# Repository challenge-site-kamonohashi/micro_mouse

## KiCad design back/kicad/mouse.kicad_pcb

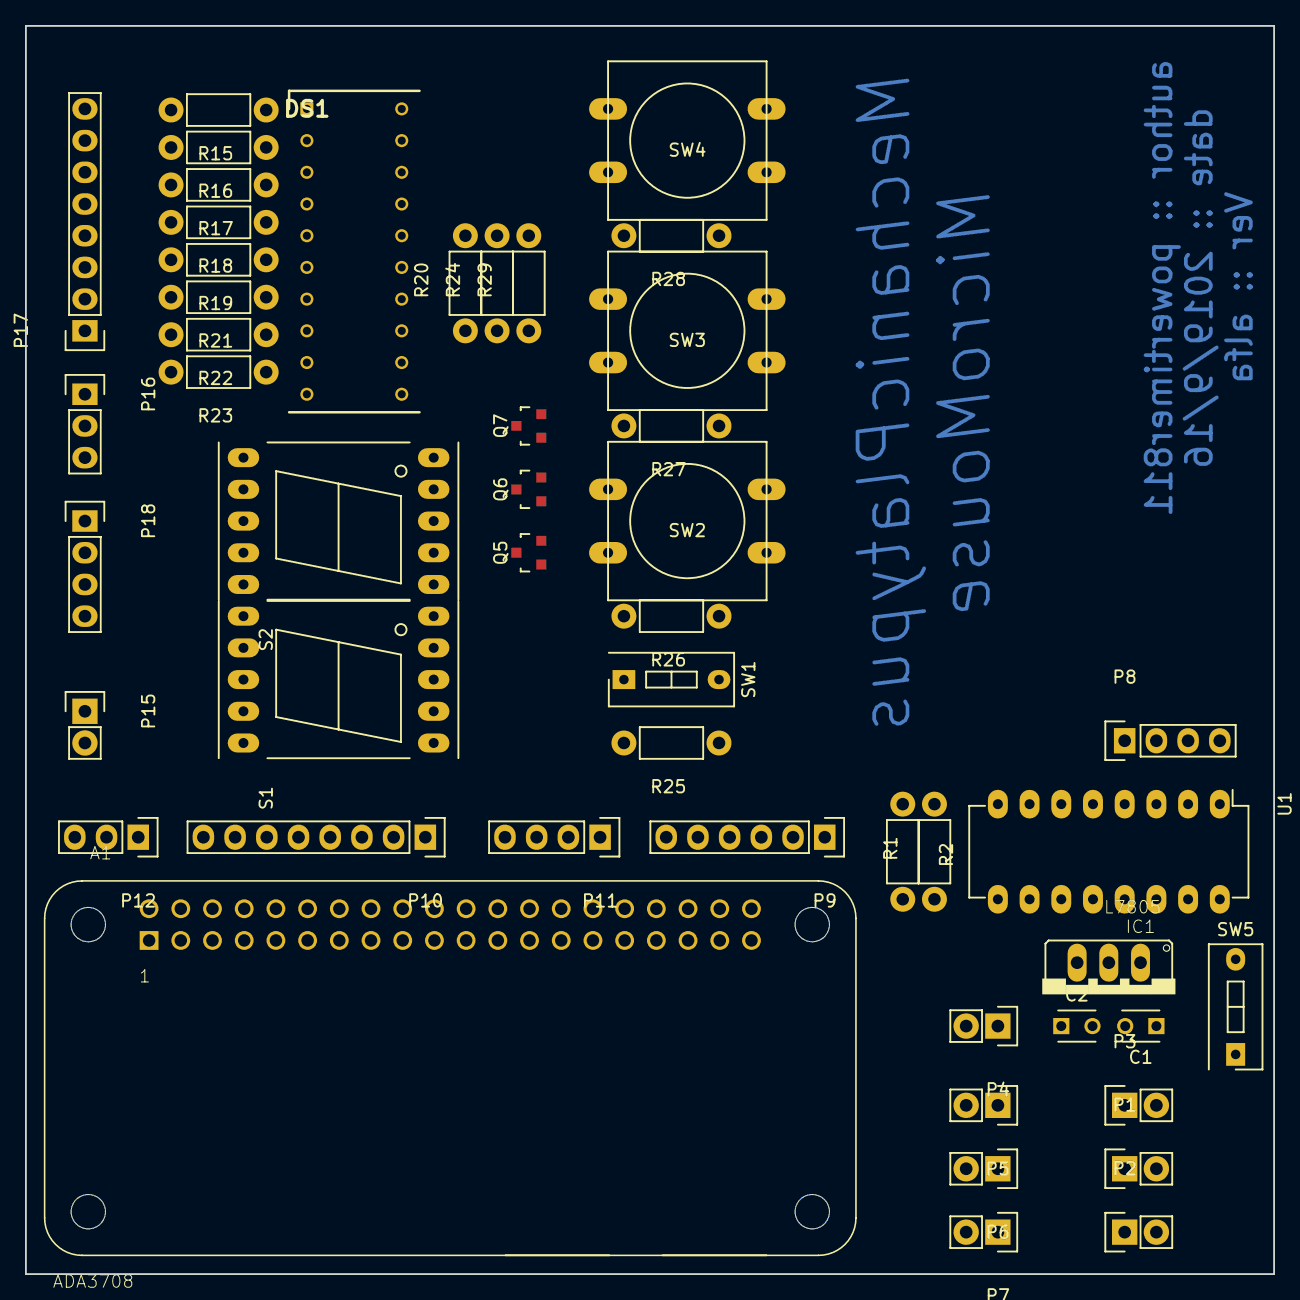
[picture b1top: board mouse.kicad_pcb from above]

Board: 2 copper layers, 100.0 x 100.0 mm, 49 parts (0 on the bottom side), 62 nets, no tracks yet.

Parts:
A1: ADA3708; ADA3708_RPI-ZERO
C1: 0.33uF; C_Disc_D3_P2.5
C2: 0.1uF; C_Disc_D3_P2.5
DS1: OSX10201-GYR1; DIPS760W45P254L2550H815Q20N
IC1: L7805; 78XXS
P1, P2: SOURCE_12v; Socket_Strip_Straight_1x02
P3: battery 12v; Socket_Strip_Straight_1x02
P4, P5, P6, P7: SOURCE_5v; Socket_Strip_Straight_1x02
P8: IR_CONN; Socket_Strip_Straight_1x04
P9: MOTOR_CONTROL; Socket_Strip_Straight_1x06
P10, P17: LED_CONN; Socket_Strip_Straight_1x08
P11, P18: SW_CONN; Socket_Strip_Straight_1x04
P12, P16: LED_K_CONN; Socket_Strip_Straight_1x03
P15: UI_SOURCE; Socket_Strip_Straight_1x02
Q5, Q6, Q7: BSS138; SOT-23
R1: 4.7k; Resistor_Horizontal_RM7mm
R2: 8.2k; Resistor_Horizontal_RM7mm
R15, R16, R17, R18, R19, R20, R21, R22, R23, R24, R25, R26, R27, R28, R29: 10k; Resistor_Horizontal_RM7mm
S1, S2: 7SEGM; 7SegmentLED_LTS6760_LTS6780
SW1, SW5: SPST; SW_DIP_x1_Slide
SW2, SW3, SW4: SW_PUSH; SW_PUSH-12mm
U1: MCP3008; DIP-16_W7.62mm_LongPads

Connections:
+5V: A1.4, C2.1, IC1.OUT, P4.2, P5.2, P6.2, P7.2, U1.15, U1.16
GND: A1.6, A1.9, A1.14, A1.20, A1.25, A1.30, A1.34, A1.39, C1.2, C2.2, IC1.GND, P1.1, P2.1, P3.1, P4.1, P5.1, P6.1, P7.1, R2.2, U1.9, U1.14
LED1: A1.3, P10.8
LED2: A1.5, P10.7
LED3: A1.7, P10.6
LED4: A1.13, P10.5
LED5: A1.15, P10.4
LED6: A1.29, P10.3
LED7: A1.31, P10.2
LED8: A1.37, P10.1
LED_K1: A1.8, P12.3
LED_K2: A1.10, P12.2
LED_K3: A1.16, P12.1
MOTOR_L_DIRE1: A1.12, P9.6
MOTOR_L_DIRE2: A1.36, P9.5
MOTOR_L_PWM: A1.32, P9.4
MOTOR_R_DIRE1: A1.11, P9.3
MOTOR_R_DIRE2: A1.35, P9.2
MOTOR_R_PWM: A1.33, P9.1
unnamed: A1.19, U1.11
unnamed: A1.21, U1.12
unnamed: A1.23, U1.13
unnamed: A1.24, U1.10
unnamed: C1.1, IC1.IN, P1.2, P2.2, R1.1, SW5.2
unnamed: DS1.1, R15.1, S1.7, S2.7
unnamed: DS1.2, R16.1, S1.6, S2.6
unnamed: DS1.3, R17.1, S1.4, S2.4
unnamed: DS1.4, R18.1, S1.2, S2.2
unnamed: DS1.5, R19.1, S1.1, S2.1
unnamed: DS1.6, R21.1, S1.9, S2.9
unnamed: DS1.7, R22.1, S1.10, S2.10
unnamed: DS1.8, R23.1, S1.5, S2.5
unnamed: DS1.11, DS1.12, DS1.13, DS1.14, DS1.15, DS1.16, DS1.17, DS1.18, DS1.19, DS1.20, Q7.3
unnamed: P3.2, SW5.1
unnamed: P8.1, U1.4
unnamed: P8.2, U1.3
unnamed: P8.3, U1.2
unnamed: P8.4, U1.1
unnamed: P15.1, Q5.2, Q6.2, Q7.2, R20.2, R24.2, R29.2, SW1.2, SW2.2, SW3.2, SW4.2
unnamed: P15.2, R25.1, R26.1, R27.1, R28.1
unnamed: P16.1, Q5.1, R20.1
unnamed: P16.2, Q6.1, R24.1
unnamed: P16.3, Q7.1, R29.1
unnamed: P17.1, R23.2
unnamed: P17.2, R22.2
unnamed: P17.3, R21.2
unnamed: P17.4, R19.2
unnamed: P17.5, R18.2
unnamed: P17.6, R17.2
unnamed: P17.7, R16.2
unnamed: P17.8, R15.2
unnamed: P18.1, R28.2, SW4.1
unnamed: P18.2, R27.2, SW3.1
unnamed: P18.3, R26.2, SW2.1
unnamed: P18.4, R25.2, SW1.1
unnamed: Q5.3, S1.3, S1.8
unnamed: Q6.3, S2.3, S2.8
unnamed: R1.2, R2.1, U1.8
SW1: A1.18, P11.4
SW2: A1.22, P11.3
SW3: A1.38, P11.2
SW4: A1.40, P11.1

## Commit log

2019-07-14 7/14
2019-07-14 7/12-2
2019-07-19 7/19
2019-08-20 add path publisher
2019-08-26 change parameter
2019-08-29 dijkstra
2019-08-30 dasda
2019-09-02 add dijkstra
2019-09-05 add a_star
2019-09-06 add fullgame
2019-09-13 change program to easy
2019-09-15 add kicad
2019-09-16 rotate raspberry pi
2019-09-16 complate kicad
2019-09-17 add bezier and spline
2019-09-17 add fastrun
2019-09-21 add worlds
2019-09-21 complate world
2019-09-24 asfd
